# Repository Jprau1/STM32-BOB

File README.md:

# STM32-BOB
This breakout-board project was created in my free time. 
- The MCU used is an STM32F070CBT6
- There are a total of 22 free GPIO ports, along with a +3.3V source and GND port on either side
- The BOB has a dedicated I2C, USART, and SPI port
- Power can be delivered through the Micro USB port or through the screw terminals
- Programs may be flashed through either the Micro USB port or Serial Wire Debug

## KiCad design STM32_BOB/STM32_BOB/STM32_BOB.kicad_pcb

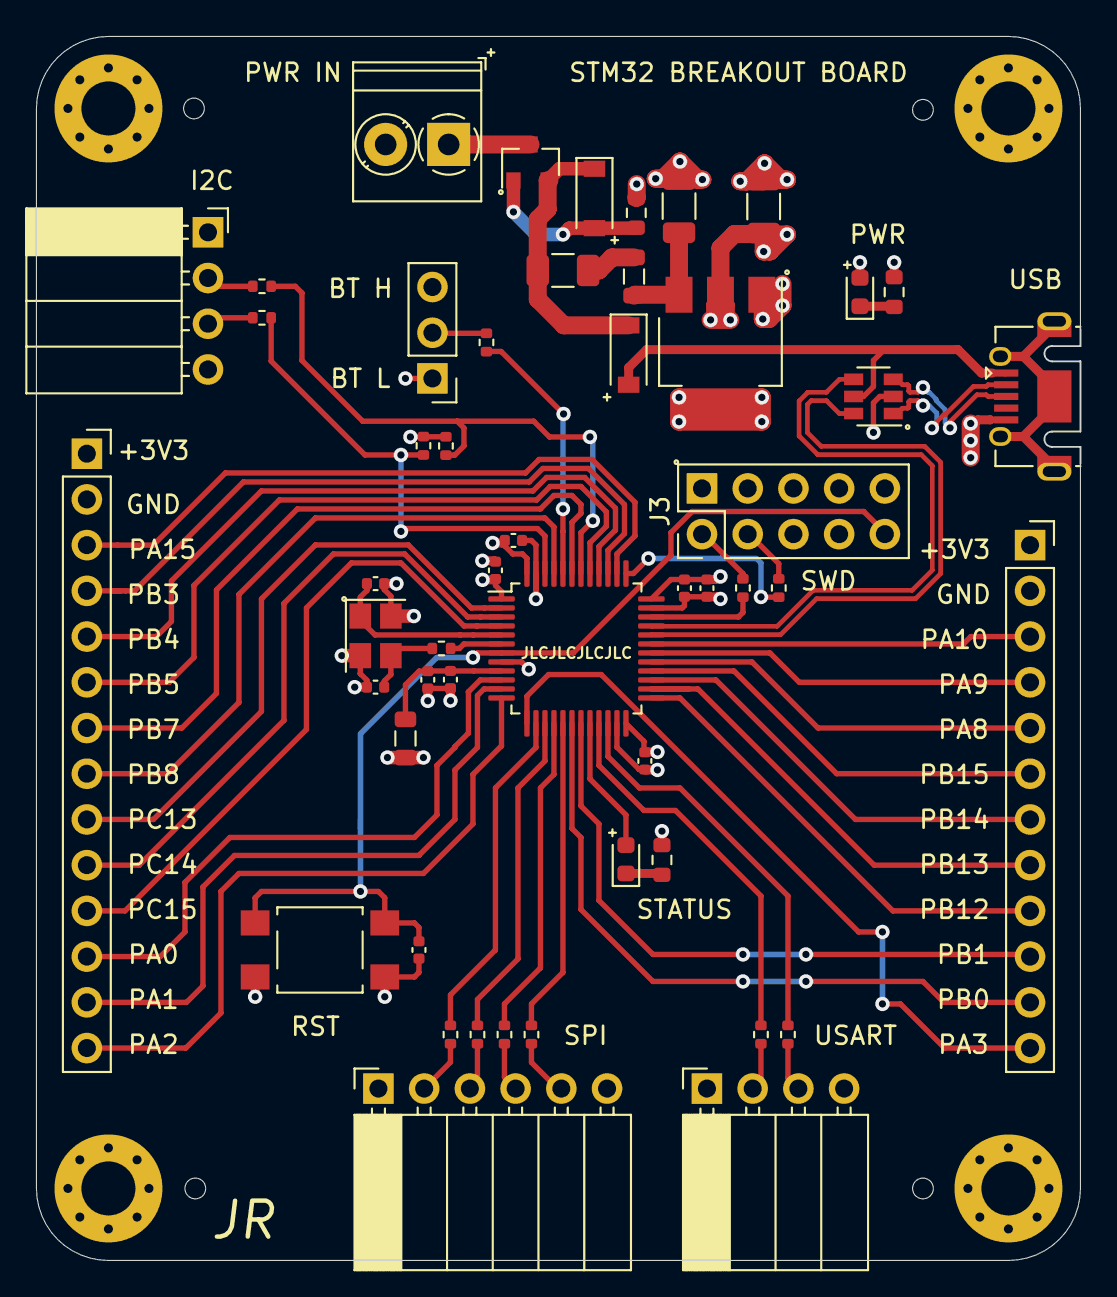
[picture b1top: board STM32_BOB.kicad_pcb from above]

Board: 4 copper layers, 58.0 x 67.9 mm, 55 parts (0 on the bottom side), 64 nets.

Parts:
C1: 100n; C_1206_3216Metric
C2: 10u; C_1206_3216Metric
C3: 4.7u; C_0402_1005Metric
C4, C5, C6, C7: 100n; C_0402_1005Metric
C8: 1u; C_0402_1005Metric
C9: 10n; C_0402_1005Metric
C10, C11: 12p; C_0402_1005Metric
C12: 0.1u; C_0402_1005Metric
D1: 11.4Vz; D_SOD-123
D2: B5819W; D_SOD-123
D3: GRN_LED_2.2V; LED_0603_1608Metric
D4: BLU_LED_3.3V; LED_0603_1608Metric
F1: 500mA; Fuse_1206_3216Metric
FB1, FB2: 100 @ 100MHz; L_0805_2012Metric
H1, H2, H3, H4: MountingHole_Pad; MountingHole_3mm_Pad_Via
HSE1: 16MHz; Crystal_SMD_3225-4Pin_3.2x2.5mm
J1: Screw_Terminal_01x02; TerminalBlock_Phoenix_PT-1,5-2-3.5-H_1x02_P3.50mm_Horizontal
J2: USB_B_Micro; USB_Micro-AB_Molex_47590-0001
J3: Conn_02x05_Odd_Even; PinHeader_2x05_P2.54mm_Vertical
J4: Conn_01x06; PinSocket_1x06_P2.54mm_Horizontal
J5, J6: Conn_01x04; PinSocket_1x04_P2.54mm_Horizontal
J7: Conn_01x12; PinSocket_1x12_P2.54mm_Vertical
J8: Conn_01x14; PinSocket_1x14_P2.54mm_Vertical
JP1: Jumper_3_Bridged12; PinHeader_1x03_P2.54mm_Vertical
Q1: AO3401A; SOT-23
R1: 330; R_0603_1608Metric
R2: 1.5k; R_0603_1608Metric
R3: 47; R_0402_1005Metric
R4: 10k; R_0402_1005Metric
R5: 2.2k; R_0603_1608Metric
R6, R7: 4.7k; R_0402_1005Metric
R8, R9, R10, R11, R12, R13, R14, R15, R16, R17: 22; R_0402_1005Metric
SW1: SW_Push; SW_SPST_TL3305A
U1: LD1117S33TR_SOT223; SOT-223-3_TabPin2
U2: USBLC6-2SC6; SOT-23-6
U3: STM32F070CBTx; LQFP-48_7x7mm_P0.5mm

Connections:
+3.3VA: C8.2, C9.2, FB2.1, U3.9
+3V3: C2.2, C3.2, C4.2, C5.2, C6.2, C7.2, D3.2, FB2.2, J3.2, J4.1, J5.1, J6.1, J7.1, J8.1, JP1.3, R6.2, R7.2, U1.2, U3.1, U3.24, U3.36, U3.48
+9V: J1.1, Q1.3
BLU_LED: D4.2, U3.20
BOOT0: R4.1, U3.44
GND: C1.1, C2.1, C3.1, C4.1, C5.1, C6.1, C7.1, C8.1, C9.1, C10.1, C11.1, C12.1, H1.1, H2.1, H3.1, H4.1, HSE1.2, HSE1.4, J1.2, J2.5, J3.4, J3.6, J3.10, J4.6, J5.4, J6.4, J7.2, J8.2, JP1.1, R1.2, R2.2, R5.2, SW1.1, U1.1, U2.2, U3.8, U3.23, U3.35, U3.47
I2C_SCL: R6.1, R14.2, U3.42
I2C_SDA: R7.1, R15.2, U3.46
NRST: C12.2, J3.9, SW1.2, U3.7
unnamed: C1.2, FB1.1, U1.3
unnamed: C11.2, HSE1.3, R3.2
unnamed: D1.1, D2.1, F1.2, Q1.2
unnamed: D1.2, Q1.1, R1.1
unnamed: D3.1, R2.1
unnamed: D4.1, R5.1
unnamed: F1.1, FB1.2
unnamed: J3.1, R8.2
unnamed: J3.3, R9.2
unnamed: J4.2, R10.1
unnamed: J4.3, R11.1
unnamed: J4.4, R12.1
unnamed: J4.5, R13.1
unnamed: J5.2, R14.1
unnamed: J5.3, R15.1
unnamed: J6.2, R16.1
unnamed: J6.3, R17.1
unnamed: JP1.2, R4.2
OSC_IN: C10.2, HSE1.1, U3.5
OSC_OUT: R3.1, U3.6
PA0: J8.12, U3.10
PA1: J8.13, U3.11
PA2: J8.14, U3.12
PA3: J7.12, U3.13
PA8: J7.5, U3.29
PA9: J7.4, U3.30
PA10: J7.3, U3.31
PA15: J8.3, U3.38
PB0: J7.11, U3.18
PB1: J7.10, U3.19
PB3: J8.4, U3.39
PB4: J8.5, U3.40
PB5: J8.6, U3.41
PB7: J8.7, U3.43
PB8: J8.8, U3.45
PB12: J7.9, U3.25
PB13: J7.8, U3.26
PB14: J7.7, U3.27
PB15: J7.6, U3.28
PC13: J8.9, U3.2
PC14: J8.10, U3.3
PC15: J8.11, U3.4
PORT_USB_D+: J2.3, U2.3
PORT_USB_D-: J2.2, U2.1
SPI1_MISO: R12.2, U3.16
SPI1_MOSI: R13.2, U3.17
SPI1_NSS: R10.2, U3.14
SPI1_SCK: R11.2, U3.15
SWCLK: R9.1, U3.37
SWDIO: R8.1, U3.34
USART3_RX: R17.2, U3.22
USART3_TX: R16.2, U3.21
USB_D+: U2.4, U3.33
USB_D-: U2.6, U3.32
VCC: D2.2, J2.1, U2.5

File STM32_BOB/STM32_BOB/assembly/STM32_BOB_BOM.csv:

Comment,Designator,Footprint,LCSC
"100n","C1","Capacitor_SMD:C_1206_3216Metric","C24497"
"12p","C10,C11","Capacitor_SMD:C_0402_1005Metric","C1547"
"0.1u","C12","Capacitor_SMD:C_0402_1005Metric","C1525"
"10u","C2","Capacitor_SMD:C_1206_3216Metric","C13585"
"4.7u","C3","Capacitor_SMD:C_0402_1005Metric","C23733"
"100n","C4,C5,C6,C7","Capacitor_SMD:C_0402_1005Metric","C1525"
"1u","C8","Capacitor_SMD:C_0402_1005Metric","C52923"
"10n","C9","Capacitor_SMD:C_0402_1005Metric","C15195"
"11.4Vz","D1","Diode_SMD:D_SOD-123","C242274"
"B5819W","D2","Diode_SMD:D_SOD-123","C8598"
"GRN_LED_2.2V","D3","LED_SMD:LED_0603_1608Metric","C72043"
"BLU_LED_3.3V","D4","LED_SMD:LED_0603_1608Metric","C72041"
"500mA","F1","Fuse:Fuse_1206_3216Metric",""
"100 @ 100MHz","FB1,FB2","Inductor_SMD:L_0805_2012Metric","C1015"
"MountingHole_Pad","H1,H2,H3,H4","MountingHole:MountingHole_3mm_Pad_Via",""
"16MHz","HSE1","Crystal:Crystal_SMD_3225-4Pin_3.2x2.5mm","C13738"
"Screw_Terminal_01x02","J1","TerminalBlock_Phoenix:TerminalBlock_Phoenix_PT-1,5-2-3.5-H_1x02_P3.50mm_Horizontal",""
"USB_B_Micro","J2","Connector_USB:USB_Micro-AB_Molex_47590-0001",""
"Conn_02x05_Odd_Even","J3","Connector_PinSocket_2.54mm:PinSocket_2x05_P2.54mm_Vertical",""
"Conn_01x06","J4","Connector_PinSocket_2.54mm:PinSocket_1x06_P2.54mm_Horizontal",""
"Conn_01x04","J5,J6","Connector_PinSocket_2.54mm:PinSocket_1x04_P2.54mm_Horizontal",""
"Conn_01x12","J7","Connector_PinSocket_2.54mm:PinSocket_1x12_P2.54mm_Vertical",""
"Conn_01x14","J8","Connector_PinSocket_2.54mm:PinSocket_1x14_P2.54mm_Vertical",""
"Jumper_3_Bridged12","JP1","Connector_PinHeader_2.54mm:PinHeader_1x03_P2.54mm_Vertical",""
"AO3401A","Q1","Package_TO_SOT_SMD:SOT-23","C15127"
"330","R1","Resistor_SMD:R_0603_1608Metric","C23138"
"1.5k","R2","Resistor_SMD:R_0603_1608Metric","C22843"
"47","R3","Resistor_SMD:R_0402_1005Metric","C25118"
"10k","R4","Resistor_SMD:R_0402_1005Metric","C25744"
"2.2k","R5","Resistor_SMD:R_0603_1608Metric","C4190"
"4.7k","R6,R7","Resistor_SMD:R_0402_1005Metric","C25900"
"22","R8,R9,R10,R11,R12,R13,R14,R15,R16,R17","Resistor_SMD:R_0402_1005Metric","C25092"
"SW_Push","SW1","Button_Switch_SMD:SW_SPST_TL3305A",""
"LD1117S33TR_SOT223","U1","Package_TO_SOT_SMD:SOT-223-3_TabPin2","C86781"
"USBLC6-2SC6","U2","Package_TO_SOT_SMD:SOT-23-6","C7519"
"STM32F070CBTx","U3","Package_QFP:LQFP-48_7x7mm_P0.5mm","C74909"
